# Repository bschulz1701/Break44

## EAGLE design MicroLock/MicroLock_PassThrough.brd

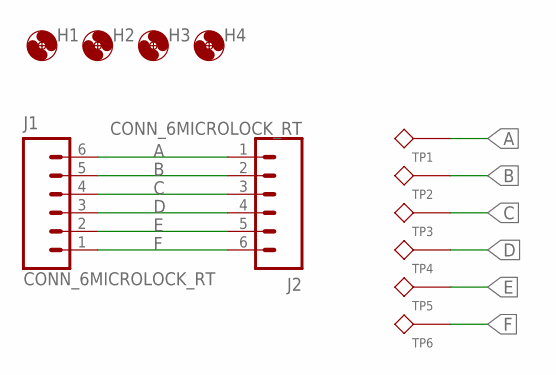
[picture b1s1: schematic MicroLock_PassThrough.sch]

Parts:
H1, H2, H3, H4: MOUNTING_HOLE2_NP; 2_56
J1, J2: CONN_6MICROLOCK_RT; 1X06_MICROLOCKPLUS_RT
TP1, TP2, TP3, TP4, TP5, TP6: TESTPOINTRCU; TESTPOINT_0603

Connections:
A: J1.6, J2.1, TP1.1
B: J1.5, J2.2, TP2.1
C: J1.4, J2.3, TP3.1
D: J1.3, J2.4, TP4.1
E: J1.2, J2.5, TP5.1
F: J1.1, J2.6, TP6.1

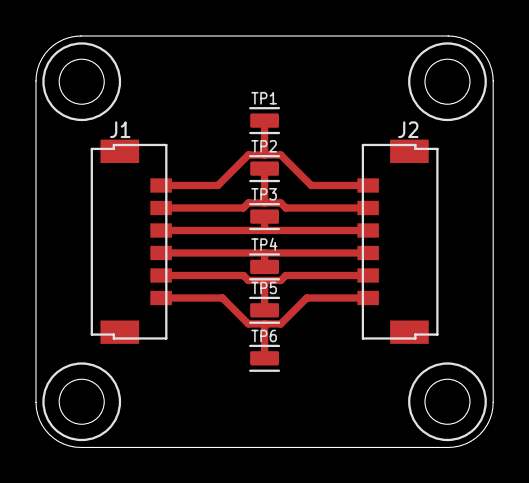
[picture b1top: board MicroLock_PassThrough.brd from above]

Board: 2 copper layers, 25.4 x 22.9 mm, 12 parts (0 on the bottom side), 6 nets.

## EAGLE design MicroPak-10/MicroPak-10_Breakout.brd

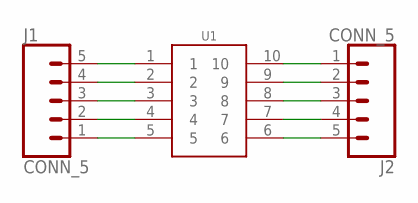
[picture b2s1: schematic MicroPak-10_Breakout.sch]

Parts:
J1, J2: CONN_5; 1X05
U1: GEN_10MICROPACK; MICROPAK_10

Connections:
unnamed: J1.5, U1.1
unnamed: J1.4, U1.2
unnamed: J1.3, U1.3
unnamed: J1.2, U1.4
unnamed: J1.1, U1.5
unnamed: J2.5, U1.6
unnamed: J2.4, U1.7
unnamed: J2.3, U1.8
unnamed: J2.2, U1.9
unnamed: J2.1, U1.10

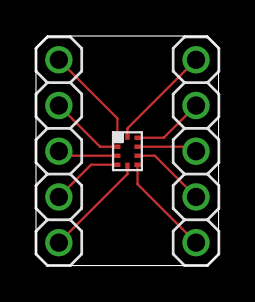
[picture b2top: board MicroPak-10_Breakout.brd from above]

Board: 2 copper layers, 10.1 x 12.8 mm, 3 parts (0 on the bottom side), 10 nets.

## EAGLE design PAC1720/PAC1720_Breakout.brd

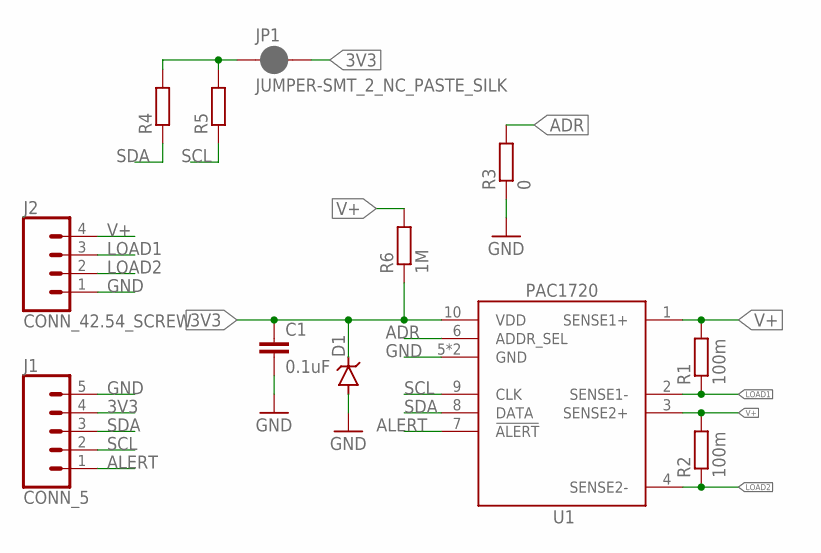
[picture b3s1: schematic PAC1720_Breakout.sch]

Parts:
C1: 0.1uF; C0402
D1: DIODE_ZENERSOD-123; SOD-123; MPN MMSZ5231B-7-F; DIGIKEY MMSZ5231B-FDICT-ND
J1: CONN_5; 1X05
J2: CONN_42.54_SCREW; 1X04_SCREW
JP1: JUMPER-SMT_2_NC_PASTE_SILK; SMT-JUMPER_2_NC_PASTE_SILK
R1, R2: 100m; R0805
R3: 0; R0402
R4, R5: R-EU_10KR0402; R0402
R6: 1M; R0402
U1: PAC1720; VDFN-10

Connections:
3V3: C1.1, D1.CAT (C), J1.4, JP1.2, R6.1, U1.10 (VDD)
ADR: R3.2, U1.6 (ADDR_SEL)
ALERT: J1.1, U1.7 (!ALERT)
GND: C1.2, D1.ANODE (A), J1.5, J2.1, R3.1, U1.5 (GND), U1.EP (GND)
LOAD1: J2.3, R1.1, U1.2 (SENSE1-)
LOAD2: J2.2, R2.1, U1.4 (SENSE2-)
unnamed: JP1.1, R4.2, R5.2
SCL: J1.2, R5.1, U1.9 (CLK)
SDA: J1.3, R4.1, U1.8 (DATA)
V+: J2.4, R1.2, R2.2, R6.2, U1.1 (SENSE1+), U1.3 (SENSE2+)

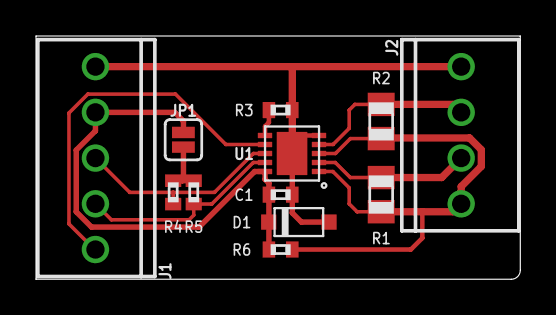
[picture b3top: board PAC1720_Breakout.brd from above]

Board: 2 copper layers, 26.9 x 13.5 mm, 12 parts (0 on the bottom side), 10 nets.

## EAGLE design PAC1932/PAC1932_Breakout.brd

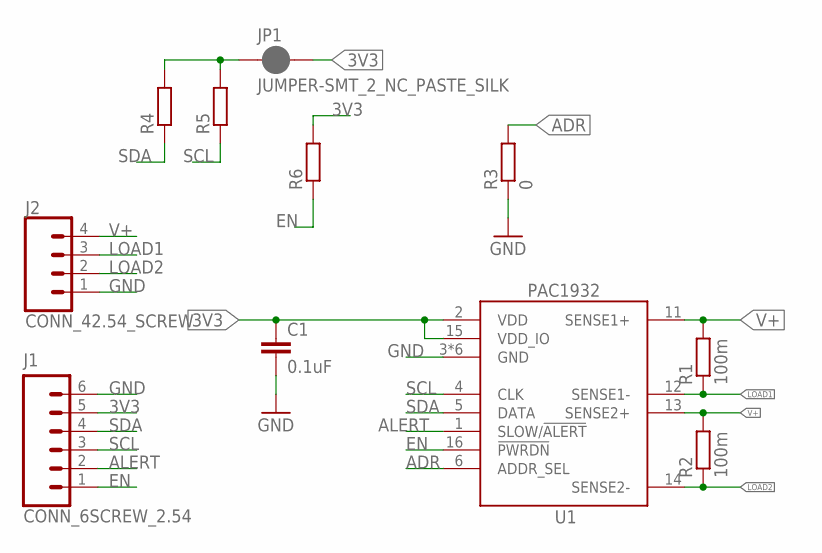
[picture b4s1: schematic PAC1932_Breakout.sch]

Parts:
C1: 0.1uF; C0402
J1: CONN_6SCREW_2.54; 1X06_SCREW
J2: CONN_42.54_SCREW; 1X04_SCREW
JP1: JUMPER-SMT_2_NC_PASTE_SILK; SMT-JUMPER_2_NC_PASTE_SILK
R1, R2: 100m; R0805
R3: 0; R0402
R4, R5, R6: R-EU_10KR0402; R0402
U1: PAC1932QFN; QFN16

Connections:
3V3: C1.1, J1.5, JP1.2, R6.2, U1.2 (VDD), U1.15 (VDD_IO)
ADR: R3.2, U1.6 (ADDR_SEL)
ALERT: J1.2, U1.1 (SLOW/!ALERT)
EN: J1.1, R6.1, U1.16 (!PWRDN)
GND: C1.2, J1.6, J2.1, R3.1, U1.3 (GND), U1.7 (GND), U1.8 (GND), U1.9 (GND), U1.10 (GND), U1.EP (GND)
LOAD1: J2.3, R1.1, U1.12 (SENSE1-)
LOAD2: J2.2, R2.1, U1.14 (SENSE2-)
unnamed: JP1.1, R4.2, R5.2
SCL: J1.3, R5.1, U1.4 (CLK)
SDA: J1.4, R4.1, U1.5 (DATA)
V+: J2.4, R1.2, R2.2, U1.11 (SENSE1+), U1.13 (SENSE2+)

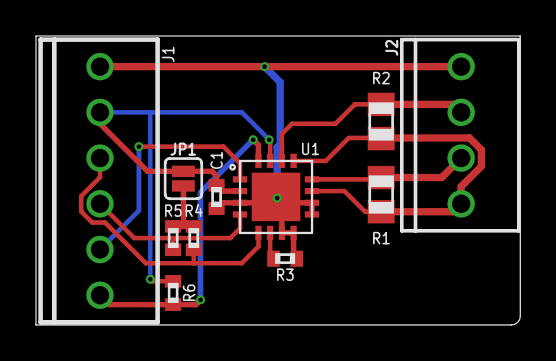
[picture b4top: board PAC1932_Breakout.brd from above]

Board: 2 copper layers, 26.9 x 16.1 mm, 11 parts (0 on the bottom side), 11 nets.

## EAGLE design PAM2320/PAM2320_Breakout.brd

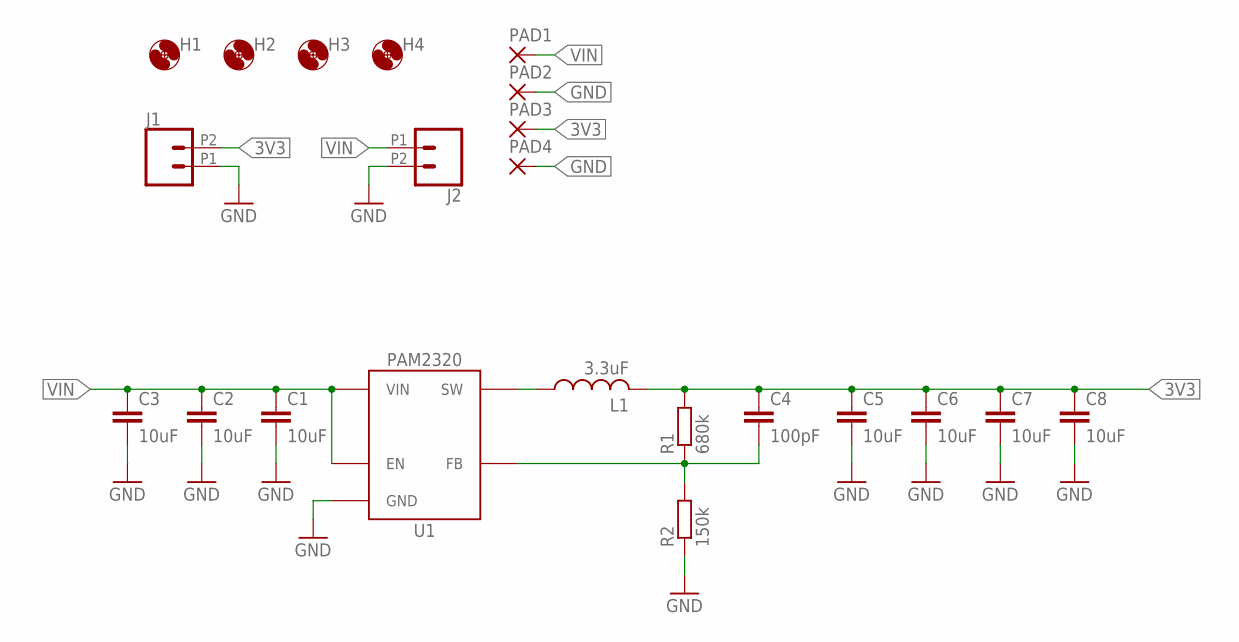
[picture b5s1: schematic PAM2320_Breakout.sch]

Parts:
C1, C2, C3, C5, C6, C7, C8: 10uF; C0805
C4: 100pF; C0603
H1, H2, H3, H4: MOUNTING_HOLE2_NP; 2_56
J1, J2: CONN_022.54_SCREW_ROUND; 1X02_2.54_SCREWTERM_ROUND
L1: 3.3uF; WE-MAPI(5.4X5.4)
PAD1, PAD2, PAD3, PAD4: SMD5; SMD2,54-5,08
R1: 680k; R0603
R2: 150k; R0603
U1: PAM2320; PSOP-8

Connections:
3V3: C4.1, C5.1, C6.1, C7.1, C8.1, J1.P2 (2), L1.P$2 (2), PAD3.1, R1.2
FB: C4.2, R1.1, R2.2, U1.5 (FB)
GND: C1.2, C2.2, C3.2, C5.2, C6.2, C7.2, C8.2, J1.P1 (1), J2.P2 (2), PAD2.1, PAD4.1, R2.1, U1.4 (GND), U1.EP (GND)
SW: L1.P$1 (1), U1.3 (SW)
VIN: C1.1, C2.1, C3.1, J2.P1 (1), PAD1.1, U1.2 (VIN), U1.7 (EN)

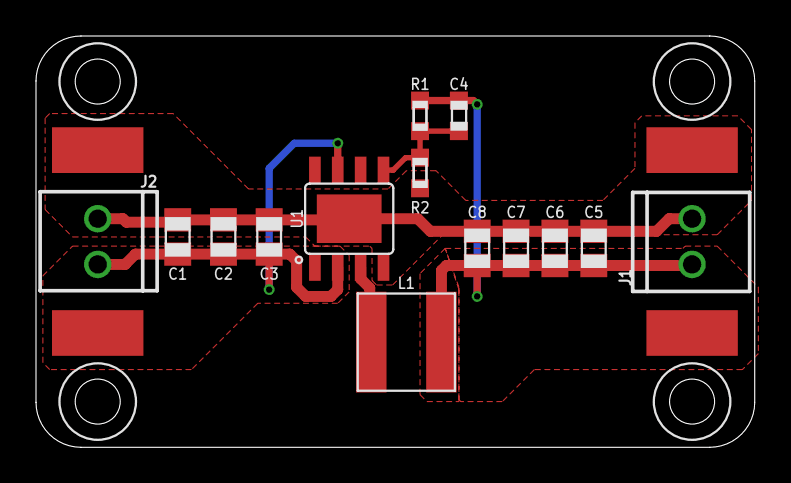
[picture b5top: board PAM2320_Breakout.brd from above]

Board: 2 copper layers, 39.9 x 22.9 mm, 22 parts (0 on the bottom side), 5 nets.

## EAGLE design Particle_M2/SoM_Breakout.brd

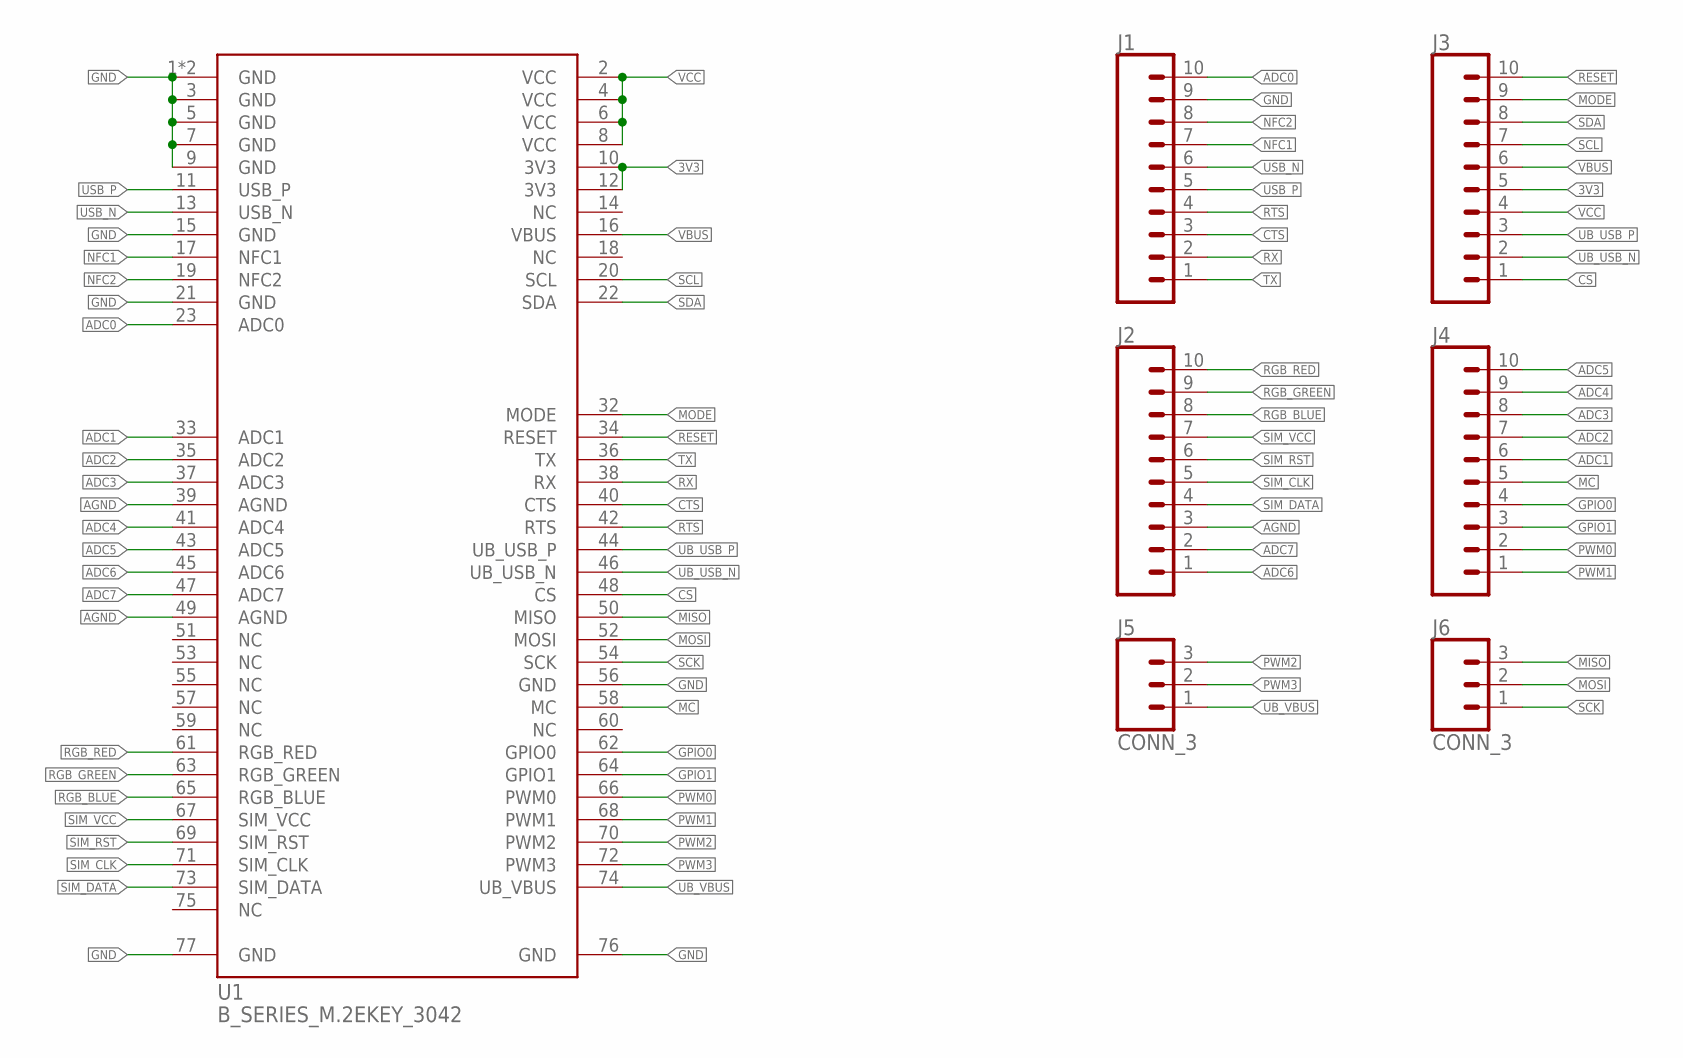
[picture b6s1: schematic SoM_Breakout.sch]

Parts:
J1, J2, J3, J4: CONN_10"; 1X10
J5, J6: CONN_3; 1X03
U1: B_SERIES_M.2EKEY_3042; PARTICLE_M.2EKEY

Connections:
3V3: J3.5, U1.10 (3V3), U1.12 (3V3)
ADC0: J1.10, U1.23 (ADC0)
ADC1: J4.6, U1.33 (ADC1)
ADC2: J4.7, U1.35 (ADC2)
ADC3: J4.8, U1.37 (ADC3)
ADC4: J4.9, U1.41 (ADC4)
ADC5: J4.10, U1.43 (ADC5)
ADC6: J2.1, U1.45 (ADC6)
ADC7: J2.2, U1.47 (ADC7)
AGND: J2.3, U1.39 (AGND), U1.49 (AGND)
CS: J3.1, U1.48 (CS)
CTS: J1.3, U1.40 (CTS)
GND: J1.9, U1.1 (GND), U1.3 (GND), U1.5 (GND), U1.7 (GND), U1.9 (GND), U1.15 (GND), U1.21 (GND), U1.56 (GND), U1.76 (GND), U1.77 (GND), U1.GND
GPIO0: J4.4, U1.62 (GPIO0)
GPIO1: J4.3, U1.64 (GPIO1)
MC: J4.5, U1.58 (MC)
MISO: J6.3, U1.50 (MISO)
MODE: J3.9, U1.32 (MODE)
MOSI: J6.2, U1.52 (MOSI)
NFC1: J1.7, U1.17 (NFC1)
NFC2: J1.8, U1.19 (NFC2)
PWM0: J4.2, U1.66 (PWM0)
PWM1: J4.1, U1.68 (PWM1)
PWM2: J5.3, U1.70 (PWM2)
PWM3: J5.2, U1.72 (PWM3)
RESET: J3.10, U1.34 (RESET)
RGB_BLUE: J2.8, U1.65 (RGB_BLUE)
RGB_GREEN: J2.9, U1.63 (RGB_GREEN)
RGB_RED: J2.10, U1.61 (RGB_RED)
RTS: J1.4, U1.42 (RTS)
RX: J1.2, U1.38 (RX)
SCK: J6.1, U1.54 (SCK)
SCL: J3.7, U1.20 (SCL)
SDA: J3.8, U1.22 (SDA)
SIM_CLK: J2.5, U1.71 (SIM_CLK)
SIM_DATA: J2.4, U1.73 (SIM_DATA)
SIM_RST: J2.6, U1.69 (SIM_RST)
SIM_VCC: J2.7, U1.67 (SIM_VCC)
TX: J1.1, U1.36 (TX)
UB_USB_N: J3.2, U1.46 (UB_USB_N)
UB_USB_P: J3.3, U1.44 (UB_USB_P)
UB_VBUS: J5.1, U1.74 (UB_VBUS)
USB_N: J1.6, U1.13 (USB_N)
USB_P: J1.5, U1.11 (USB_P)
VBUS: J3.6, U1.16 (VBUS)
VCC: J3.4, U1.2 (VCC), U1.4 (VCC), U1.6 (VCC), U1.8 (VCC)

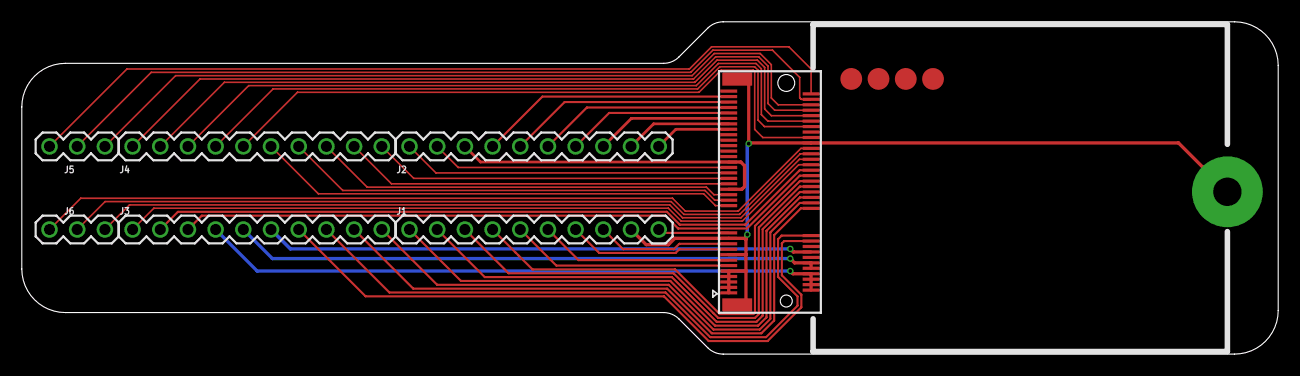
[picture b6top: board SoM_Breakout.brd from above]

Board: 2 copper layers, 115.2 x 30.5 mm, 7 parts (0 on the bottom side), 46 nets.

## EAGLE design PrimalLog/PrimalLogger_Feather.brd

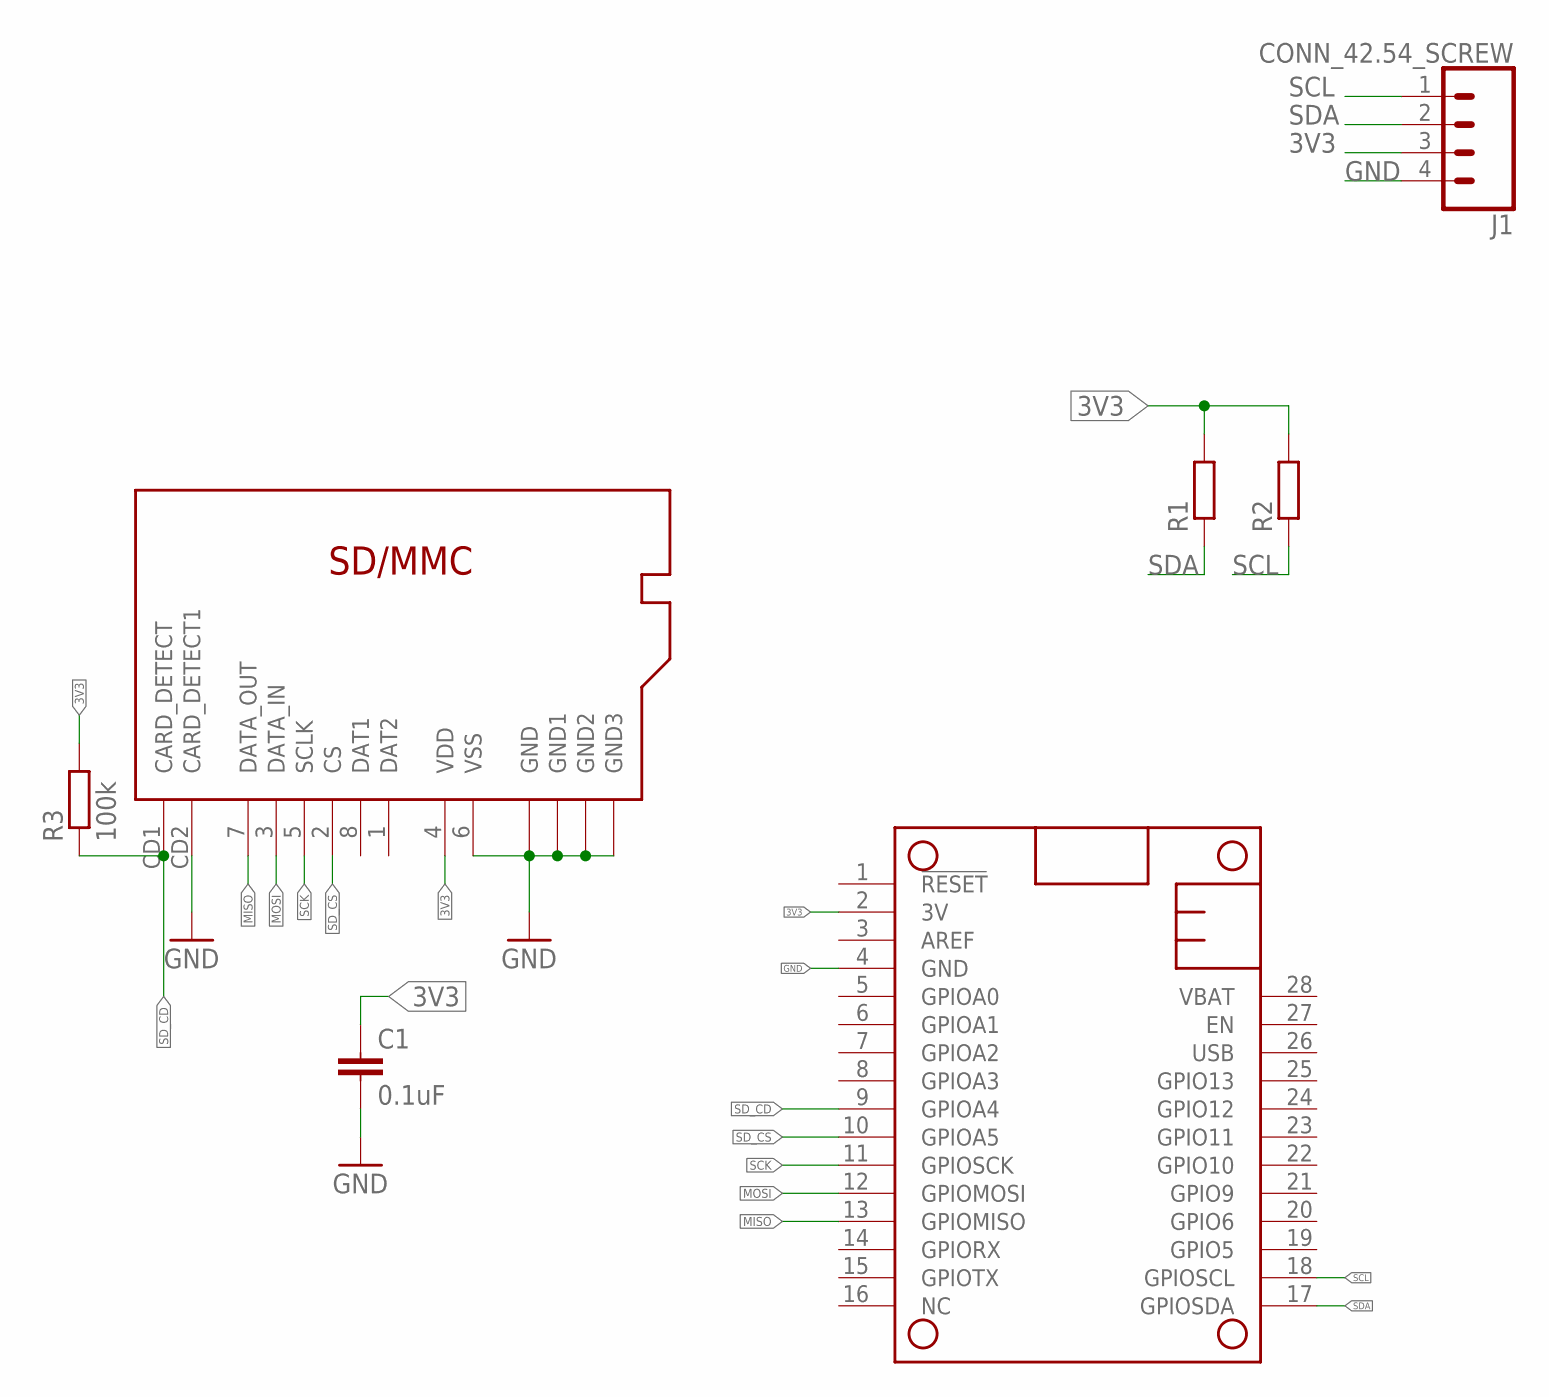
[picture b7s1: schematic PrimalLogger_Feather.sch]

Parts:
C1: 0.1uF; C0603
J1: CONN_42.54_SCREW; 1X04_SCREW
MS1: FEATHERWING_NODIM; FEATHERWING_DIM
R1, R2: R-EU_10KR0603; R0603
R3: 100k; R0603
SD1: MICRO_SD; CUSTOM-PARTS_SD_MICRO

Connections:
3V3: C1.1, J1.3, MS1.2 (3V), R1.2, R2.2, R3.2, SD1.4 (VDD)
GND: C1.2, J1.4, MS1.4 (GND), SD1.6 (VSS), SD1.CD2 (CARD_DETECT1), SD1.GND@1 (GND), SD1.GND@2 (GND1), SD1.GND@3 (GND2), SD1.GND@5 (GND3)
MISO: MS1.13 (GPIOMISO), SD1.7 (DATA_OUT)
MOSI: MS1.12 (GPIOMOSI), SD1.3 (DATA_IN)
SCK: MS1.11 (GPIOSCK), SD1.5 (SCLK)
SCL: J1.1, MS1.18 (GPIOSCL), R2.1
SDA: J1.2, MS1.17 (GPIOSDA), R1.1
SD_CD: MS1.9 (GPIOA4), R3.1, SD1.CD1 (CARD_DETECT)
SD_CS: MS1.10 (GPIOA5), SD1.2 (CS)

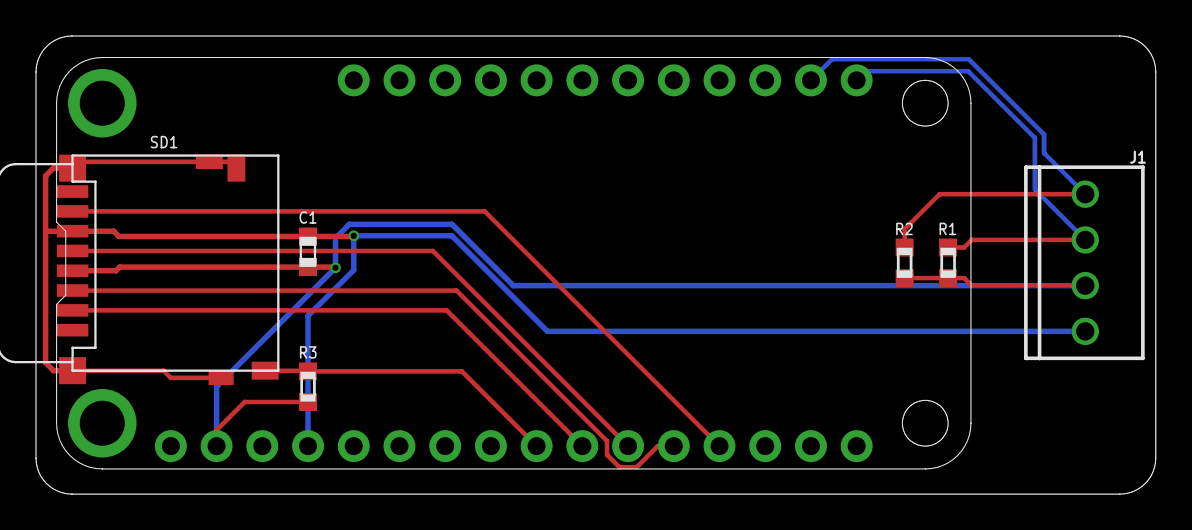
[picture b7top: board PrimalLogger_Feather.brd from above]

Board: 2 copper layers, 62.2 x 25.5 mm, 7 parts (0 on the bottom side), 9 nets.

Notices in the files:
parts and their libraries:
SparkFun-Jumpers: Licensing: Creative Commons ShareAlike 4.0 International - https://creativecommons.org/licenses/by-sa/4.0
Particle-Devices: Licensing: Designed by Particle.
